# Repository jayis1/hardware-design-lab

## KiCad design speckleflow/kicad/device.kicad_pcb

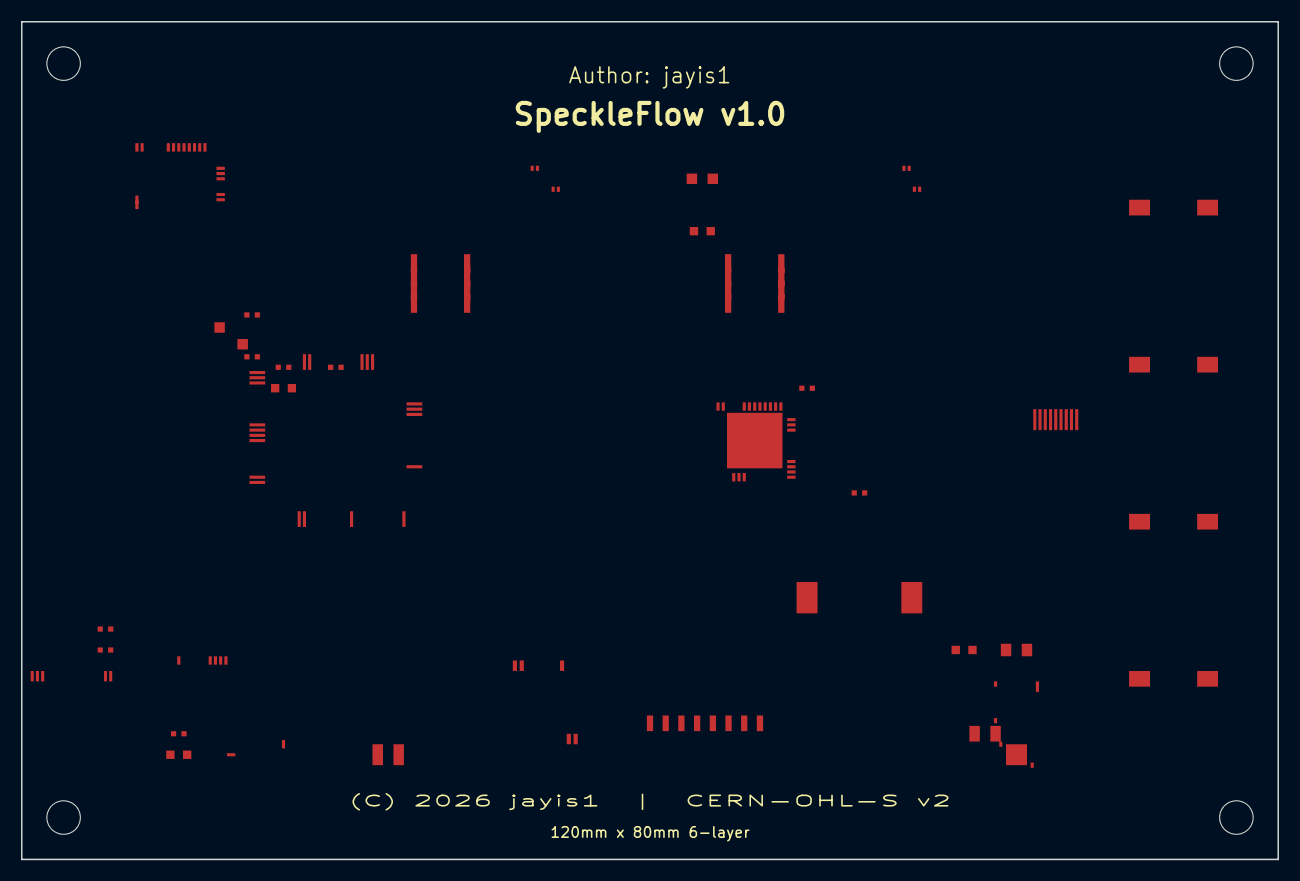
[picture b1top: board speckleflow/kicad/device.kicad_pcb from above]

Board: 6 copper layers, 120.0 x 80.0 mm, 37 parts (0 on the bottom side), 39 nets, no tracks yet.

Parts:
BT1: LiPo_2000mAh; JST_PH2_B2B-PH-K_1x02_P2.00mm
C1, C2: 100nF; C_0402_1005Metric
C3: 4.7µF; C_0603_1608Metric
C4: 10µF; C_0805_2012Metric
C5: 1µF; C_0603_1608Metric
C6, C7: 22pF; C_0402_1005Metric
D1: MP-3021T; TEC_30x30mm
D2: Vixar_V800_785nm_30mW; VCSEL_TO46
D3: LED_Blue; LED_0603_1608Metric
D4: LED_Red; LED_0603_1608Metric
J1: USB_C_Receptacle; USB_C_Receptacle_HRO_TYPE-C-31-M-12
J2: Micro_SD_Card; microSD_HC_Hirose_DM3D-SF
L1: 2.2µH; L_0805_2012Metric
R1, R2: 10kΩ; R_0402_1005Metric
R3, R4: 5k1Ω; R_0402_1005Metric
R5: 330Ω; R_0402_1005Metric
SW1: Trigger; SW_SPST_B3SN_6x6mm
SW2: Mode; SW_SPST_B3SN_6x6mm
SW3: Up; SW_SPST_B3SN_6x6mm
SW4: Down; SW_SPST_B3SN_6x6mm
U1: STM32H733VIT6; LQFP-100_14x14mm_P0.5mm
U2: iCE40UP5K-SG48; QFN-48-1EP_7x7mm_P0.5mm_EP5.3x5.3mm
U3: OV9281; OV9281_LGA
U4: nRF52840; nordic_nRF52840_qfn73
U5: ILI9341; Hirose_FH12-14S-0.5SH_1x14-1MP_P0.5mm
U7: MAX1968; TSSOP-24_4.4x7.8mm_P0.65mm
U8: MCP73871; QFN-20-1EP_4x4mm_P0.5mm
U9: TPS63020; VQFN-14-1EP_3x3mm_P0.5mm
U10: ICM-42688-P; QFN-14-1EP_3x2.5mm_P0.5mm
U11: MAX17048; TDFN-8-1EP_2x2mm_P0.5mm
U12: W25Q128; SOIC-8_3.9x4.9mm_P1.27mm
U13: MCP4921; SOIC-8_3.9x4.9mm_P1.27mm
Y1: 25MHz; Crystal_SMD_3225-4Pin_3.2x2.5mm

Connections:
+3V3: C1.1, C3.1, C5.1, J2.4, L1.2, R1.1, R5.2, U1.2, U1.100, U3.2, U4.1, U5.2, U7.2, U9.8, U10.1, U12.4, U12.7, U12.8, U13.1, U13.8
+VBAT: BT1.1, C4.1, L1.1, U8.10, U8.11, U9.1, U11.1
+VUSB: J1.A4, J1.B9, R4.2, U8.1
CAM_DVP_D0: U2.10, U3.10
CAM_DVP_D1: U2.11, U3.11
CAM_DVP_D2: U2.12, U3.12
CAM_DVP_D3: U2.13, U3.13
CAM_DVP_D4: U2.14, U3.14
CAM_DVP_D5: U2.15, U3.15
CAM_DVP_D6: U2.16, U3.16
CAM_DVP_D7: U2.17, U3.17
CAM_HSYNC: U2.21, U3.21
CAM_PCLK: U2.20, U3.20
CAM_PWDN: U1.90, U3.30
CAM_VSYNC: U2.22, U3.22
CAM_XSHUT: U1.91, U3.31
DAC1_OUT: D2.1, U1.40, U13.5
FPGA_CDONE: U1.81, U2.41
FPGA_CRST: R2.2, U1.82, U2.42
FPGA_IRQ: U1.80, U2.40
GND: BT1.2, C1.2, C2.2, C3.2, C4.2, C5.2, C6.2, C7.2, D2.2, D3.2, D4.2, J1.A1, J1.B12, J2.1, J2.6, R3.1, R4.1, SW1.1, SW2.1, SW3.1, SW4.1, U1.1, U2.49, U3.1, U4.50, U5.1, U7.1, U8.20, U9.15, U10.2, U11.2, U12.3, U13.3, U13.6
I2C1_SCL: U1.30, U3.25
I2C1_SDA: U1.31, U3.26
I2C4_SCL: U10.10, U11.5
I2C4_SDA: U10.11, U11.6
LED_STATUS: D3.1, R5.1
OSC_IN: C6.1, Y1.1
OSC_OUT: C7.1, Y1.3
R5K1_CC1: J1.A5, R3.2
SPI1_MISO: J2.7, U1.11, U2.32, U12.5, U13.4
SPI1_MOSI: J2.3, U1.12, U2.31, U12.2
SPI1_NSS: J2.2, R1.2, U1.13, U2.33, U12.1, U13.2
SPI1_SCK: J2.5, U1.10, U2.30, U12.6, U13.7
TEC_A: D1.1, U7.15
TEC_B: D1.2, U7.16
TIM8_CH1: U1.60, U7.10
USART3_RX: U1.21, U4.11
USART3_TX: U1.20, U4.10
VDD_3V3_FPGA: C2.1, R2.1, U2.1

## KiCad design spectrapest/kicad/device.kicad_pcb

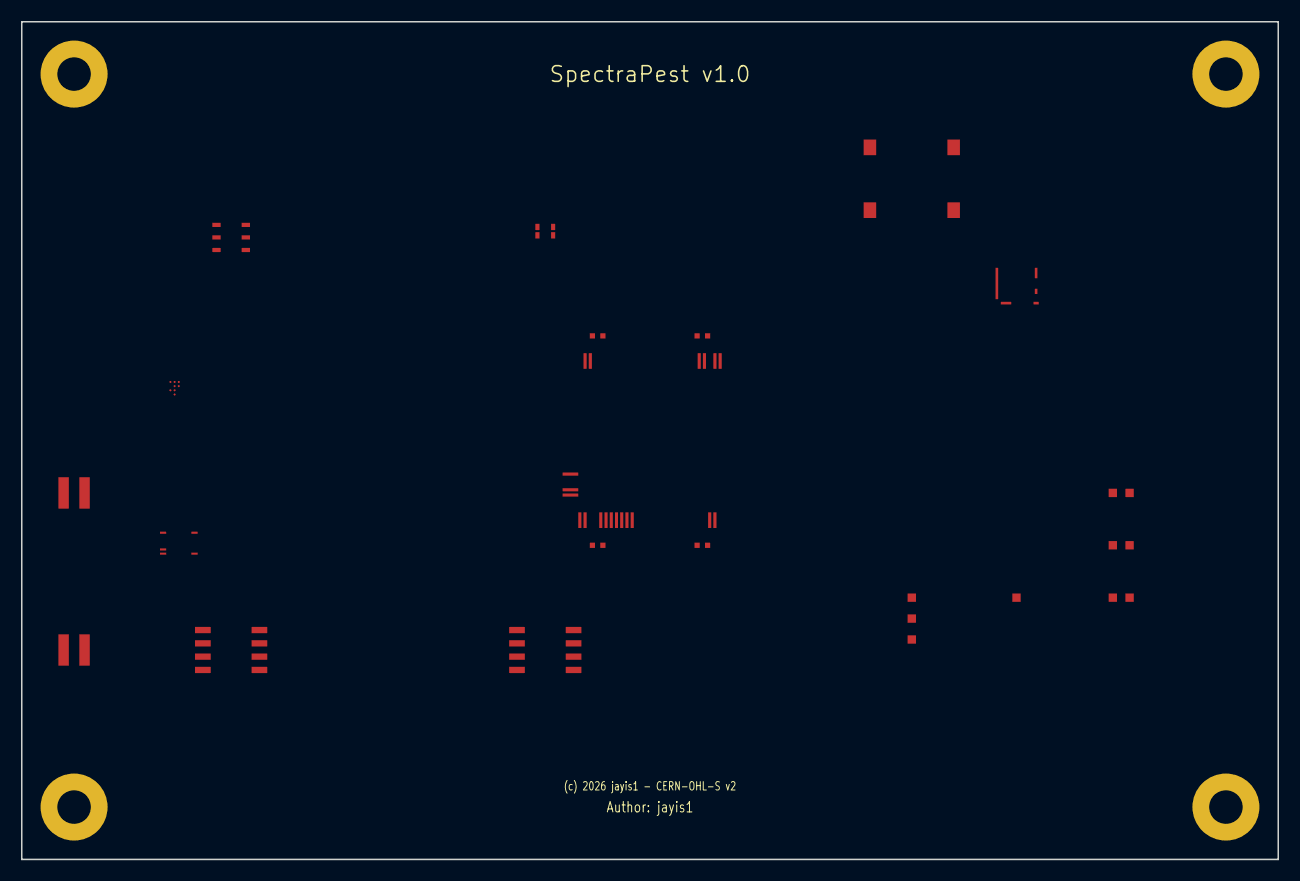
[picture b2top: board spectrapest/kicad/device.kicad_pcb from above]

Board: 4 copper layers, 120.0 x 80.0 mm, 19 parts (0 on the bottom side), 15 nets, no tracks yet.

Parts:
C1, C2, C3, C4: 0.1uF; C_0402_1005Metric
D1: Green_Status; LED_0603_1608Metric
D2: Blue_Activity; LED_0603_1608Metric
D3: Red_Error; LED_0603_1608Metric
J1: Solar_Panel; JST_PH_S2B-PH-K_1x02_P2.00mm_Horizontal
J2: Battery_LiFePO4; JST_PH_S2B-PH-K_1x02_P2.00mm_Horizontal
U1: STM32H753VIT6; LQFP-100_14x14mm_P0.5mm
U3: SX1262IMLTRT; QFN-24-1EP_4x4mm_P0.5mm
U5: SPH0645LU4H-1; LGA-6_3x4mm_P1.2mm
U6: W25Q128JVSIQ; SOIC-8_3.9x4.9mm_P1.27mm
U7: MB85RS2MTA; SOIC-8_3.9x4.9mm_P1.27mm
U8: MAX77654; WLP-30_2.55x2.08mm_P0.4mm
U9: MAX17055; TDFN-14-1EP_3x3mm_P0.4mm
U10: NEO-M9N; ublox_NEO
U12: SHT45-AD1B-R2; Sensirion_DFN-4-EP_2.5x2.5mm_P1mm
U15: SCD41; Sensirion_SCD-4x_10.1x10.1mm

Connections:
+3V3: C1.1, C2.1, C3.1, C4.1, D1.2, D2.2, D3.2, U1.11, U1.19, U1.28, U1.50, U1.75, U1.100, U3.5, U3.16, U5.4, U6.8, U7.8, U8.B1, U9.14, U12.1
+5V: U8.B2, U10.8, U15.1
GND: C1.2, C2.2, C3.2, C4.2, J1.2, J2.2, U1.10, U1.27, U1.49, U1.74, U1.99, U3.17, U3.24, U5.5, U6.4, U7.3, U7.4, U8.C1, U9.8, U10.1, U12.4, U15.2
GNSS_RXD: U1.26, U10.3
GNSS_TXD: U1.25, U10.2
I2C_SCL: U1.94, U8.B4, U9.6, U12.3, U15.4
I2C_SDA: U1.93, U8.B3, U9.5, U12.2, U15.3
LORA_BUSY: U1.36, U3.7
LORA_DIO1: U1.35, U3.8
LORA_MISO: U1.31, U3.3, U6.2
LORA_MOSI: U1.32, U3.4, U6.5
LORA_NSS: U1.29, U3.1
LORA_SCK: U1.30, U3.2, U6.6
VDD_BATT: J2.1, U8.A1, U9.1
VDD_SOLAR: J1.1, U8.A3

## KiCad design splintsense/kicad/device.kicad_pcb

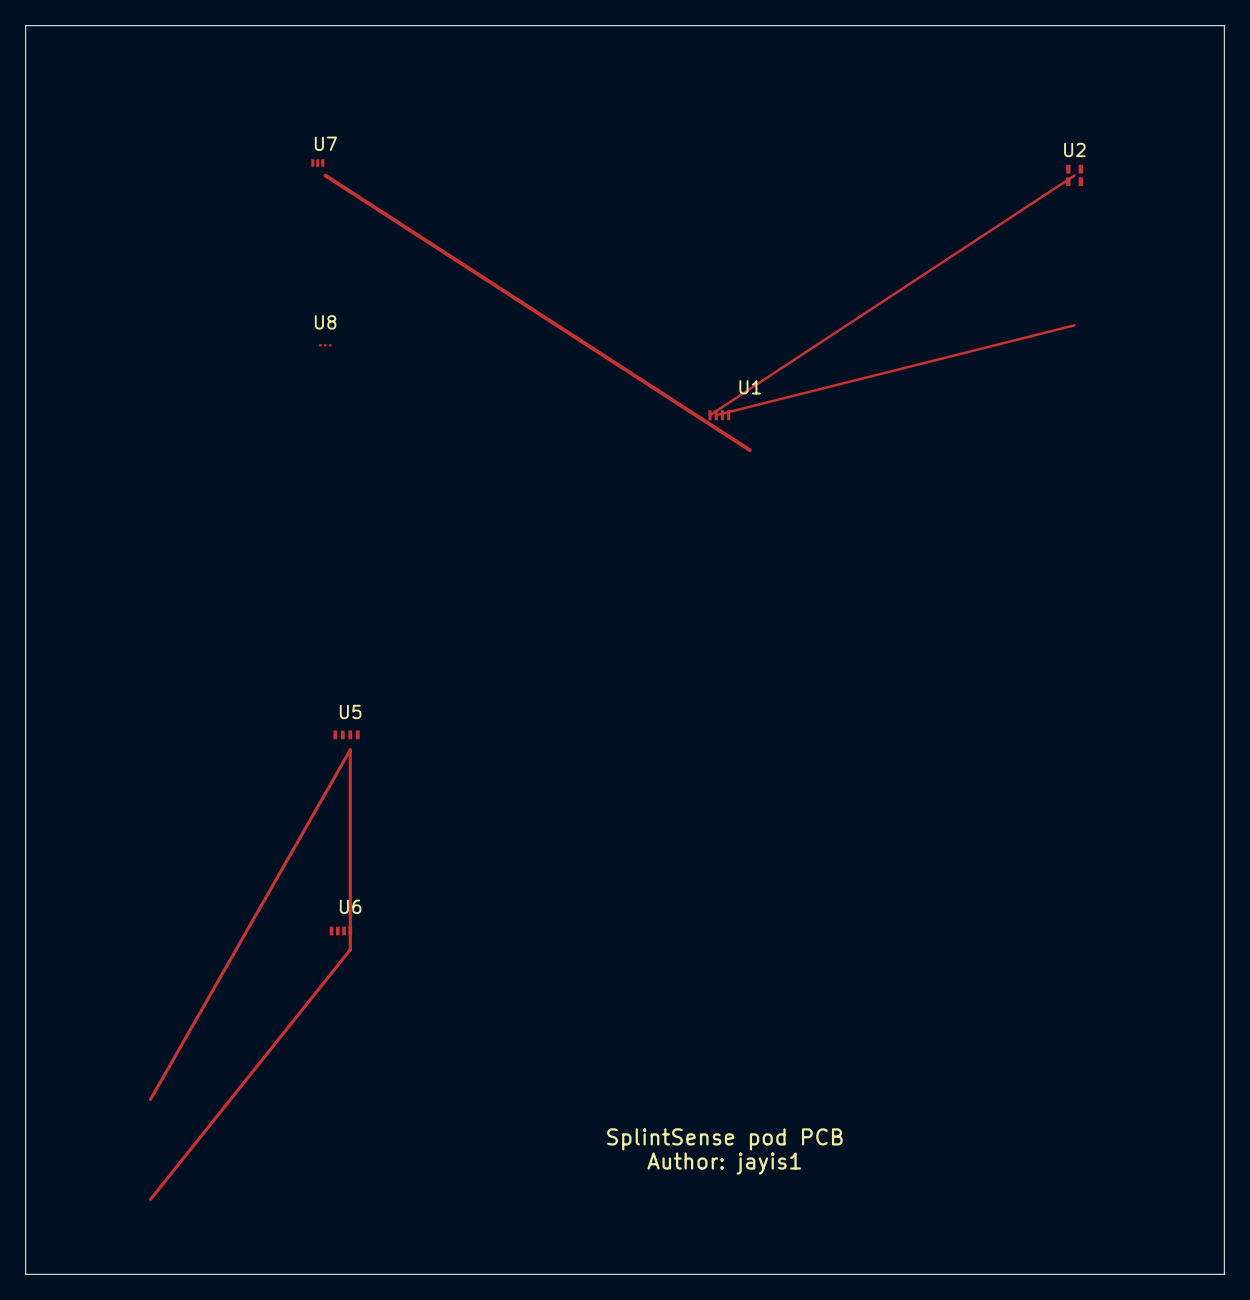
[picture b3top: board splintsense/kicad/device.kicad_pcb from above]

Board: 2 copper layers, 96.0 x 100.0 mm, 6 parts (0 on the bottom side), 4 nets.

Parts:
U1: nRF5340-QKAA; QFN-94-EP_7x7mm_P0.5mm
U2: SHT45; DFN-4_1.5x1.5mm_P0.65mm
U5: FDC2214; QFN-16-1EP_3x3mm_P0.5mm_EP1.7x1.7mm
U6: AD7147; LFCSP-24-1EP_4x4mm_P0.5mm_EP2.5x2.5mm
U7: BQ25185; WSON-16-1EP_2.5x2.5mm_P0.4mm_EP1.5x1.5mm
U8: DRV2605L; DSBGA-9_1.3x1.3mm_Layout3x3_P0.4mm

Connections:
3V3: U1.3, U2.3, U5.4, U6.4, U7.2
GND: U1.4, U2.4, U7.3
I2C_SCL: U1.1, U2.1, U5.2, U6.2, U8.A2
I2C_SDA: U1.2, U2.2, U5.3, U6.3, U8.A3

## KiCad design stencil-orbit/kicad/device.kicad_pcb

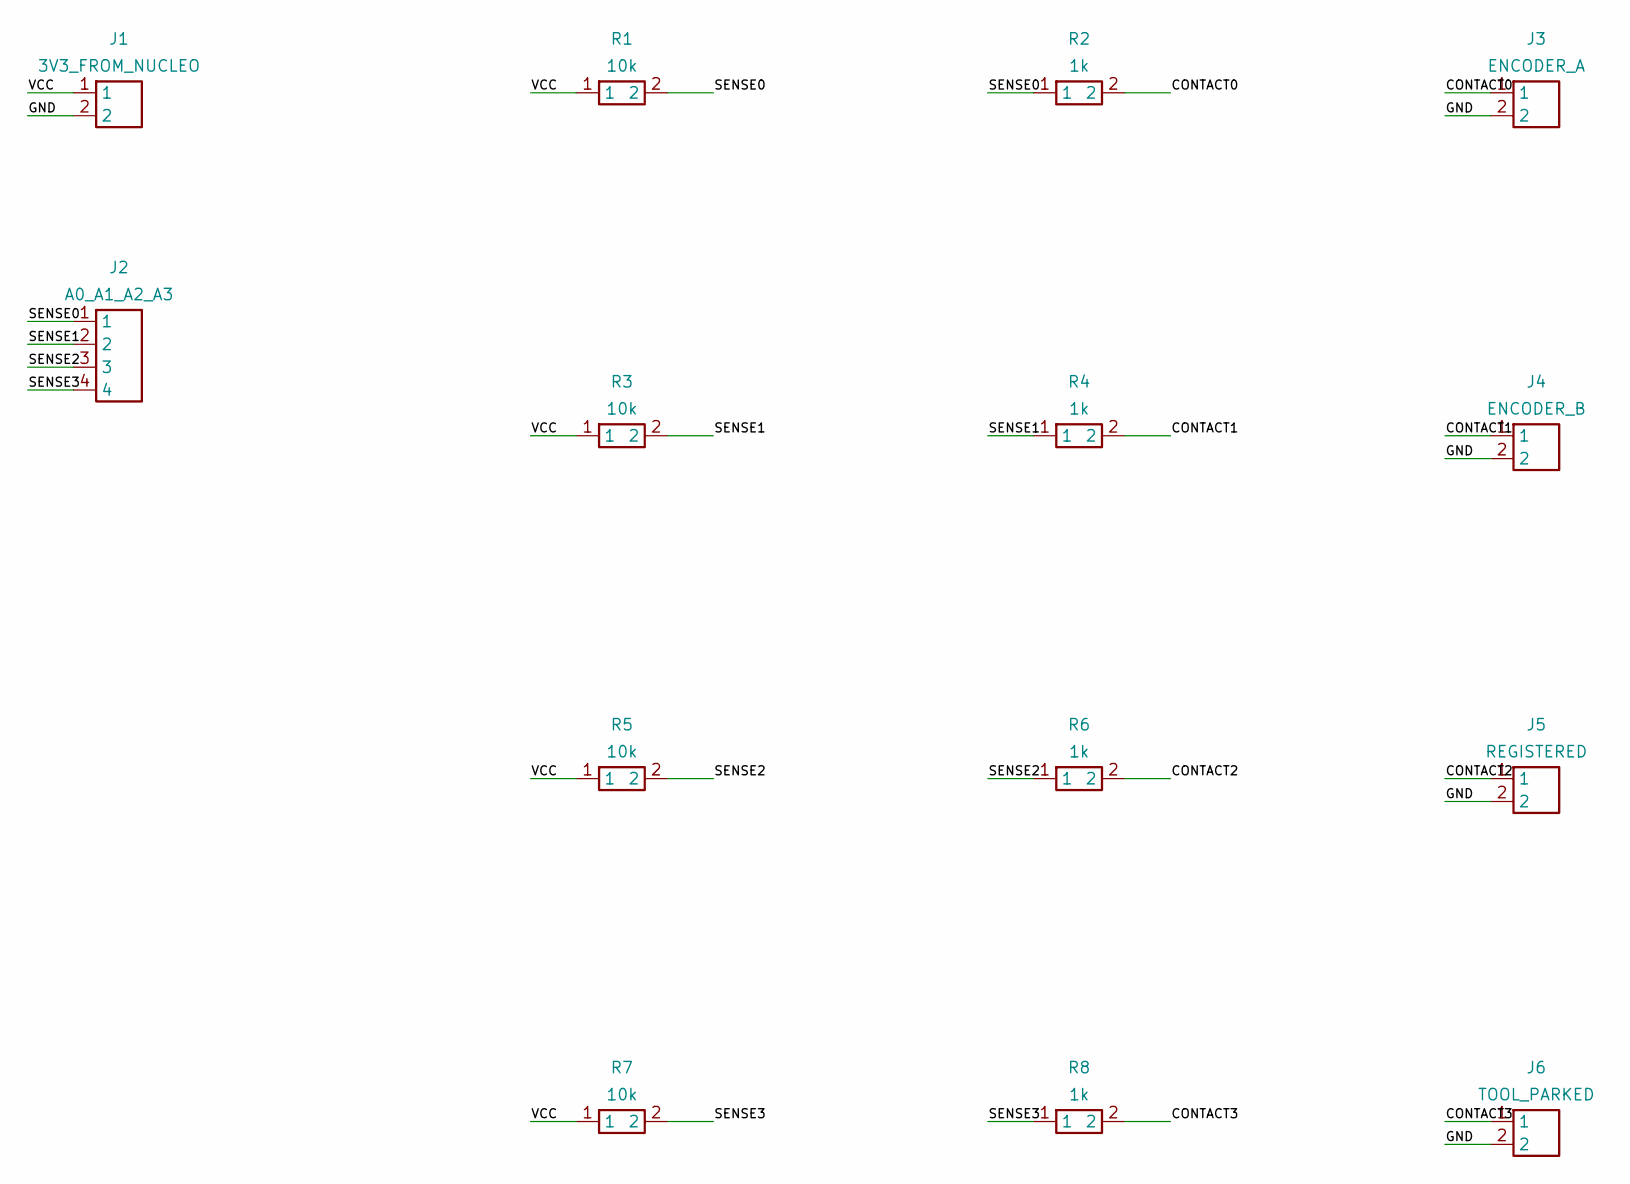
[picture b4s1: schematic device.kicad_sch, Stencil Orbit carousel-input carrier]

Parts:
J1: 3V3_FROM_NUCLEO; PinHeader_1x02_P2.54mm_Vertical
J2: A0_A1_A2_A3; PinHeader_1x04_P2.54mm_Vertical
J3: ENCODER_A; PinHeader_1x02_P2.54mm_Vertical
J4: ENCODER_B; PinHeader_1x02_P2.54mm_Vertical
J5: REGISTERED; PinHeader_1x02_P2.54mm_Vertical
J6: TOOL_PARKED; PinHeader_1x02_P2.54mm_Vertical
R1, R3, R5, R7: 10k; R_Axial_DIN0207_L6.3mm_D2.5mm_P7.62mm_Horizontal
R2, R4, R6, R8: 1k; R_Axial_DIN0207_L6.3mm_D2.5mm_P7.62mm_Horizontal

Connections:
CONTACT0: J3.1, R2.2
CONTACT1: J4.1, R4.2
CONTACT2: J5.1, R6.2
CONTACT3: J6.1, R8.2
GND: J1.2, J3.2, J4.2, J5.2, J6.2
SENSE0: J2.1, R1.2, R2.1
SENSE1: J2.2, R3.2, R4.1
SENSE2: J2.3, R5.2, R6.1
SENSE3: J2.4, R7.2, R8.1
VCC: J1.1, R1.1, R3.1, R5.1, R7.1

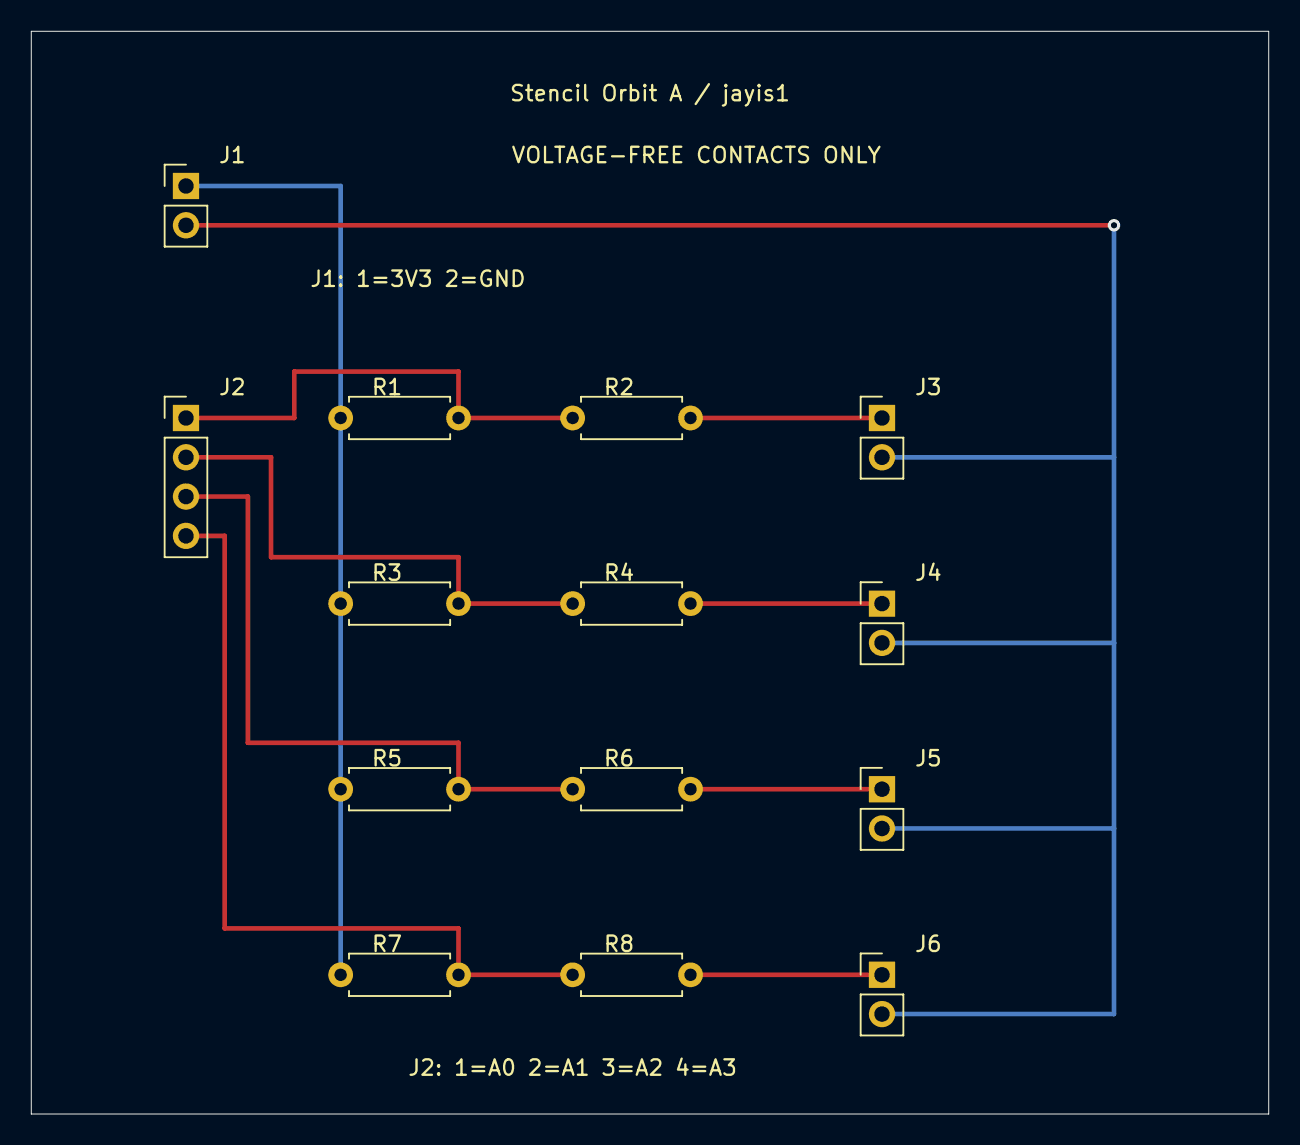
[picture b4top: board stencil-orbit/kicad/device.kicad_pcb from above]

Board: 2 copper layers, 80.0 x 70.0 mm, 14 parts (0 on the bottom side), 10 nets.

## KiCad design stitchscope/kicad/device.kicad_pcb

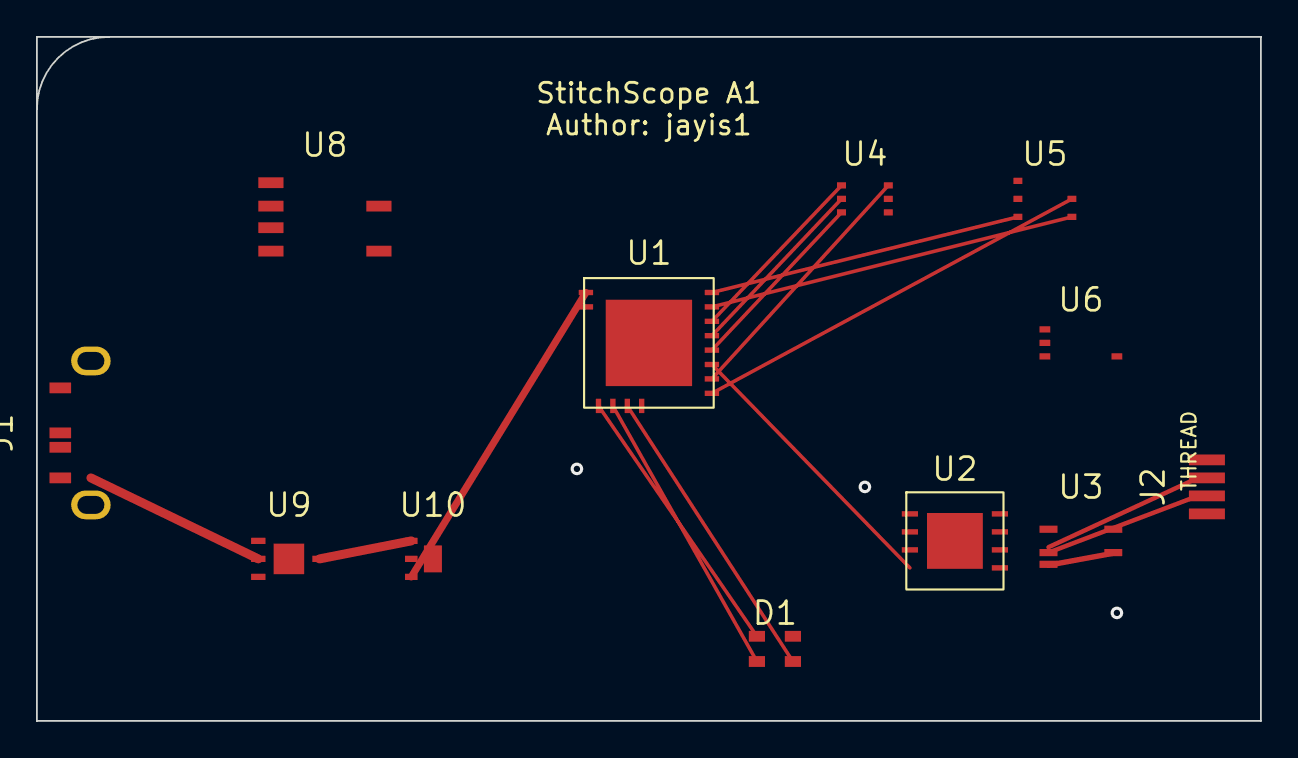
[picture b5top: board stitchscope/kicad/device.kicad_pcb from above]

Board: 4 copper layers, 68.0 x 38.0 mm, 12 parts (0 on the bottom side), 19 nets.

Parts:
D1: RGB; LED_RGB_1210
J1: USB-C; USB_C_Receptacle_GCT_USB4105-xx-A_16P_TopMnt_Horizontal
J2: THREAD_GATE; JST_SH_SM04B-SRSS-TB_1x04-1MP_P1.00mm_Horizontal
U1: nRF5340-QKAA; QFN-94-1EP_7x7mm_P0.4mm
U2: ADS131M02; VQFN-32-1EP_5x5mm_P0.5mm
U3: INA333; VSSOP-8_3x3mm_P0.65mm
U4: IIS3DWB; LGA-14_3x2.5mm_P0.5mm
U5: MMC5603NJ; LGA-16_3x3mm_P0.5mm
U6: TMF8821; LGA-12_4.6x2.0mm_P0.5mm
U8: W25Q64JV; DFN-8-1EP_6x5mm_P1.27mm
U9: BQ24074; WSON-16-1EP_3x3mm_P0.5mm
U10: TPS62840; WSON-8-1EP_2x3mm_P0.5mm

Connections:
+3V0: D1.4, J2.1, U1.1, U2.1, U3.7, U4.8, U5.1, U6.1, U8.8, U10.3
ACCEL_INT: U1.16, U4.4
ADC_DRDY: U1.15, U2.18
BAT: U9.2, U9.8, U10.1
FORCE_AMP: U2.3, U3.6
FORCE_N: J2.3, U3.2
FORCE_P: J2.2, U3.3
GND: J1.A12, J1.S1, J1.S2, J2.4, U1.2, U1.94, U2.2, U2.33, U3.4, U4.7, U5.2, U6.2, U8.4, U9.3, U9.17, U10.2, U10.9
HALL_INT: U1.17, U5.5
I2C_SCL: U1.10, U5.3, U6.3
I2C_SDA: U1.11, U5.4, U6.4
LED_B: D1.3, U1.23
LED_G: D1.2, U1.22
LED_R: D1.1, U1.21
QSPI_CS: U1.20, U8.1
SPI_MISO: U1.14, U2.15, U4.3, U8.2
SPI_MOSI: U1.13, U2.16, U4.2, U8.3
SPI_SCK: U1.12, U2.17, U4.1, U8.6
VBUS: J1.A4, U9.1

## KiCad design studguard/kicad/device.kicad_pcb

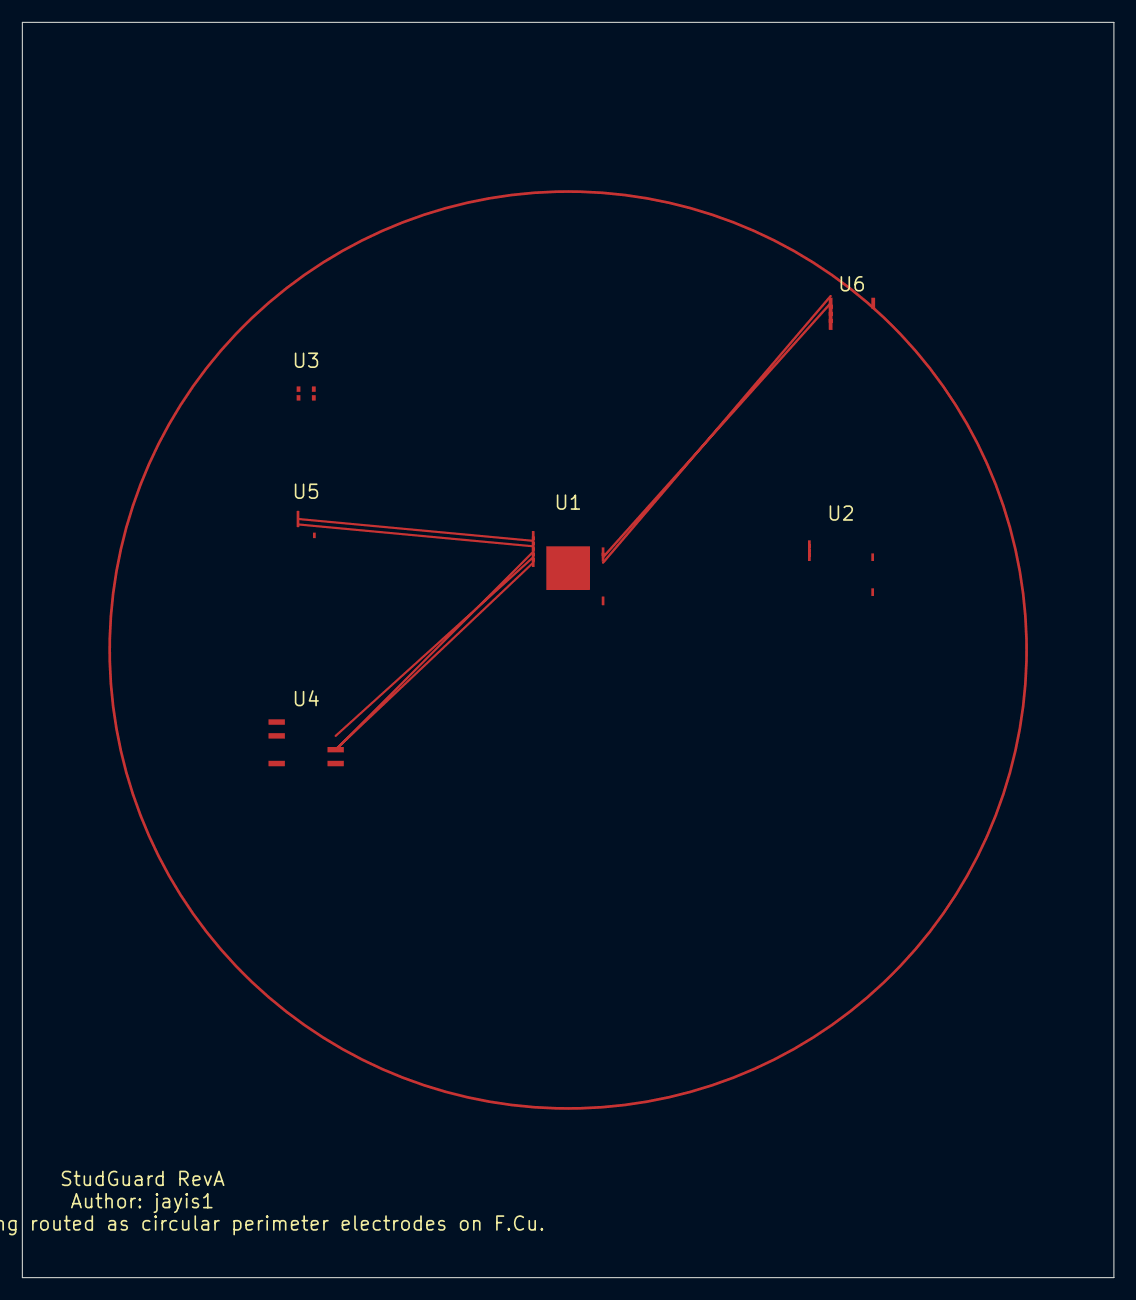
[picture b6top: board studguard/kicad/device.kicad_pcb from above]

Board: 2 copper layers, 100.0 x 115.0 mm, 7 parts (1 on the bottom side), 9 nets.

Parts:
BT1: LiPo_1200mAh; BatteryHolder_Keystone_2993
U1: nRF5340-QKAA; QFN-94-1EP_7x7mm_P0.5mm
U2: DW3110; QFN-48-1EP_6x6mm_P0.4mm
U3: SHT41; DFN-4_1.5x1.5mm_P0.8mm
U4: W25Q64JV; SOIC-8_3.9x4.9mm_P1.27mm
U5: LIS2DW12; LGA-12_2x2mm_P0.5mm
U6: TLV9062; TSSOP-8_3x3mm_P0.65mm

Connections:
3V3: U1.1, U2.1, U3.1, U4.8, U5.1, U6.8
ADC_IN: U1.22, U6.1
GND: BT1.2, U1.47, U1.EP, U2.48, U3.4, U4.4, U5.12, U6.2, U6.4
I2C_SCL: U1.3, U3.3, U5.2
I2C_SDA: U1.2, U3.2, U5.3
PIEZO_DRV: U1.21, U6.3
SPI_MISO: U1.5, U2.3, U4.2
SPI_MOSI: U1.4, U2.2, U4.1
SPI_SCK: U1.6, U2.4, U4.6

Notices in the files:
speckleflow/kicad/device.kicad_pcb:
Copyright (C) 2026 jayis1
License: CERN-OHL-S v2
(C) 2026 jayis1  |  CERN-OHL-S v2
speckleflow/kicad/device.kicad_sch:
Author: jayis1  |  Copyright (C) 2026 jayis1  |  License: CERN-OHL-S v2
spectrapest/kicad/device.kicad_pcb:
Copyright (c) 2026 jayis1. All rights reserved.
stratascan/kicad/device.kicad_sch:
Author: jayis1 — Copyright 2026
